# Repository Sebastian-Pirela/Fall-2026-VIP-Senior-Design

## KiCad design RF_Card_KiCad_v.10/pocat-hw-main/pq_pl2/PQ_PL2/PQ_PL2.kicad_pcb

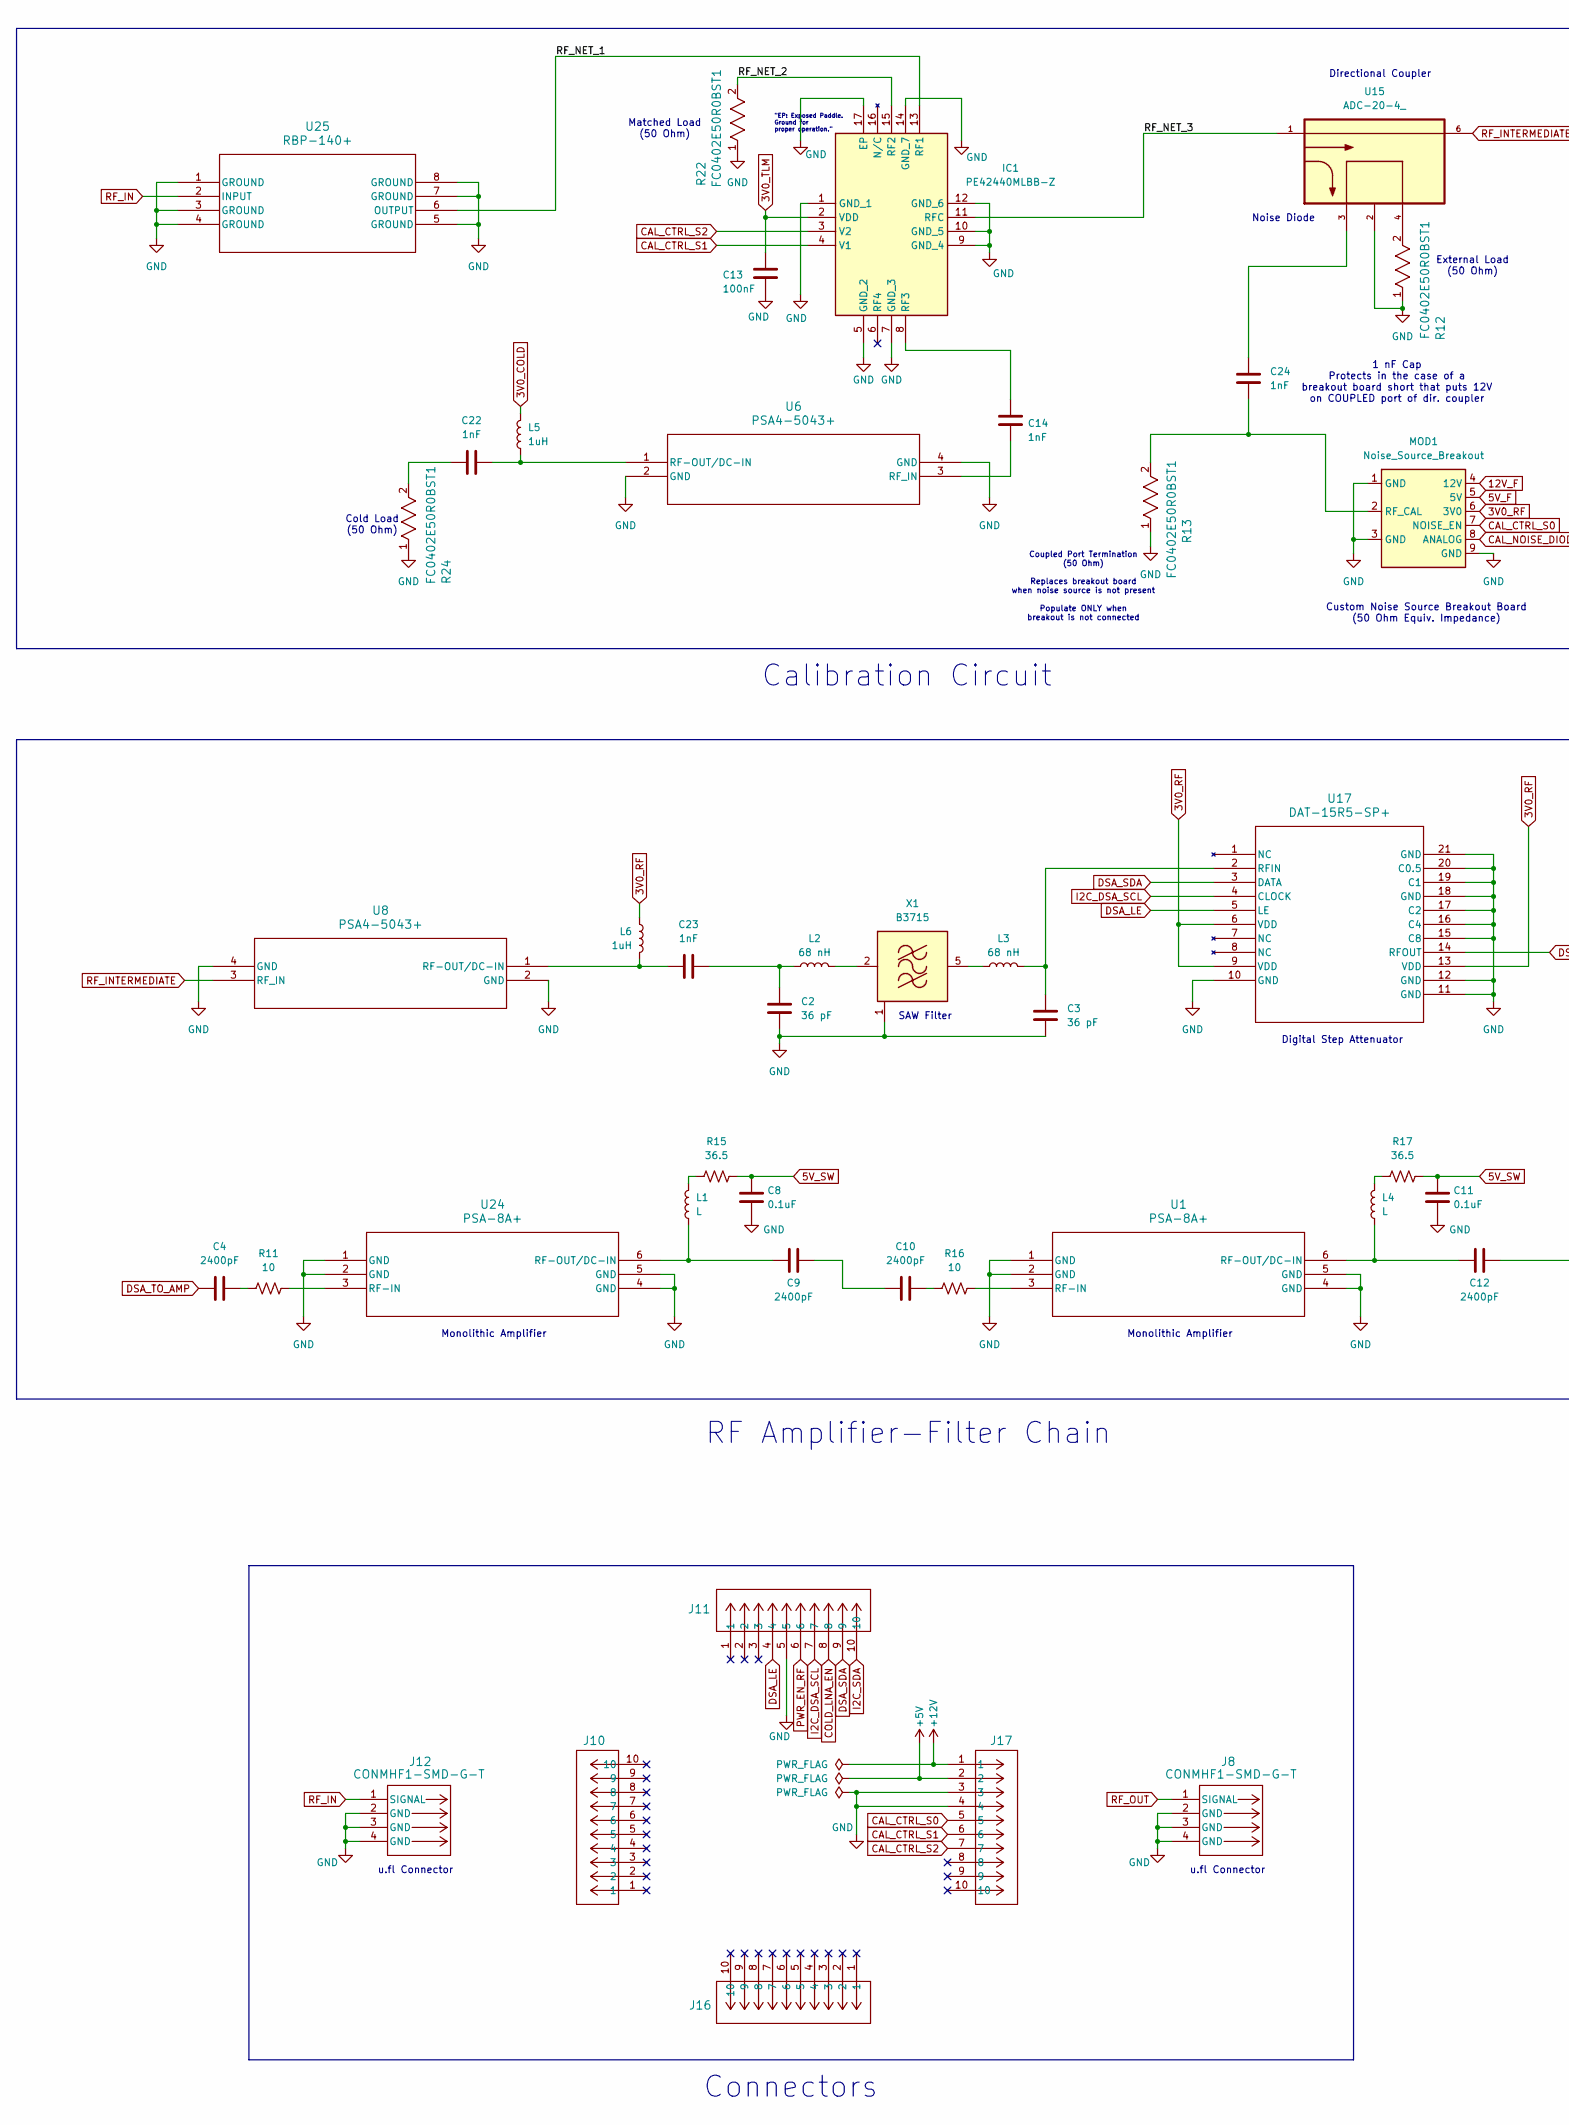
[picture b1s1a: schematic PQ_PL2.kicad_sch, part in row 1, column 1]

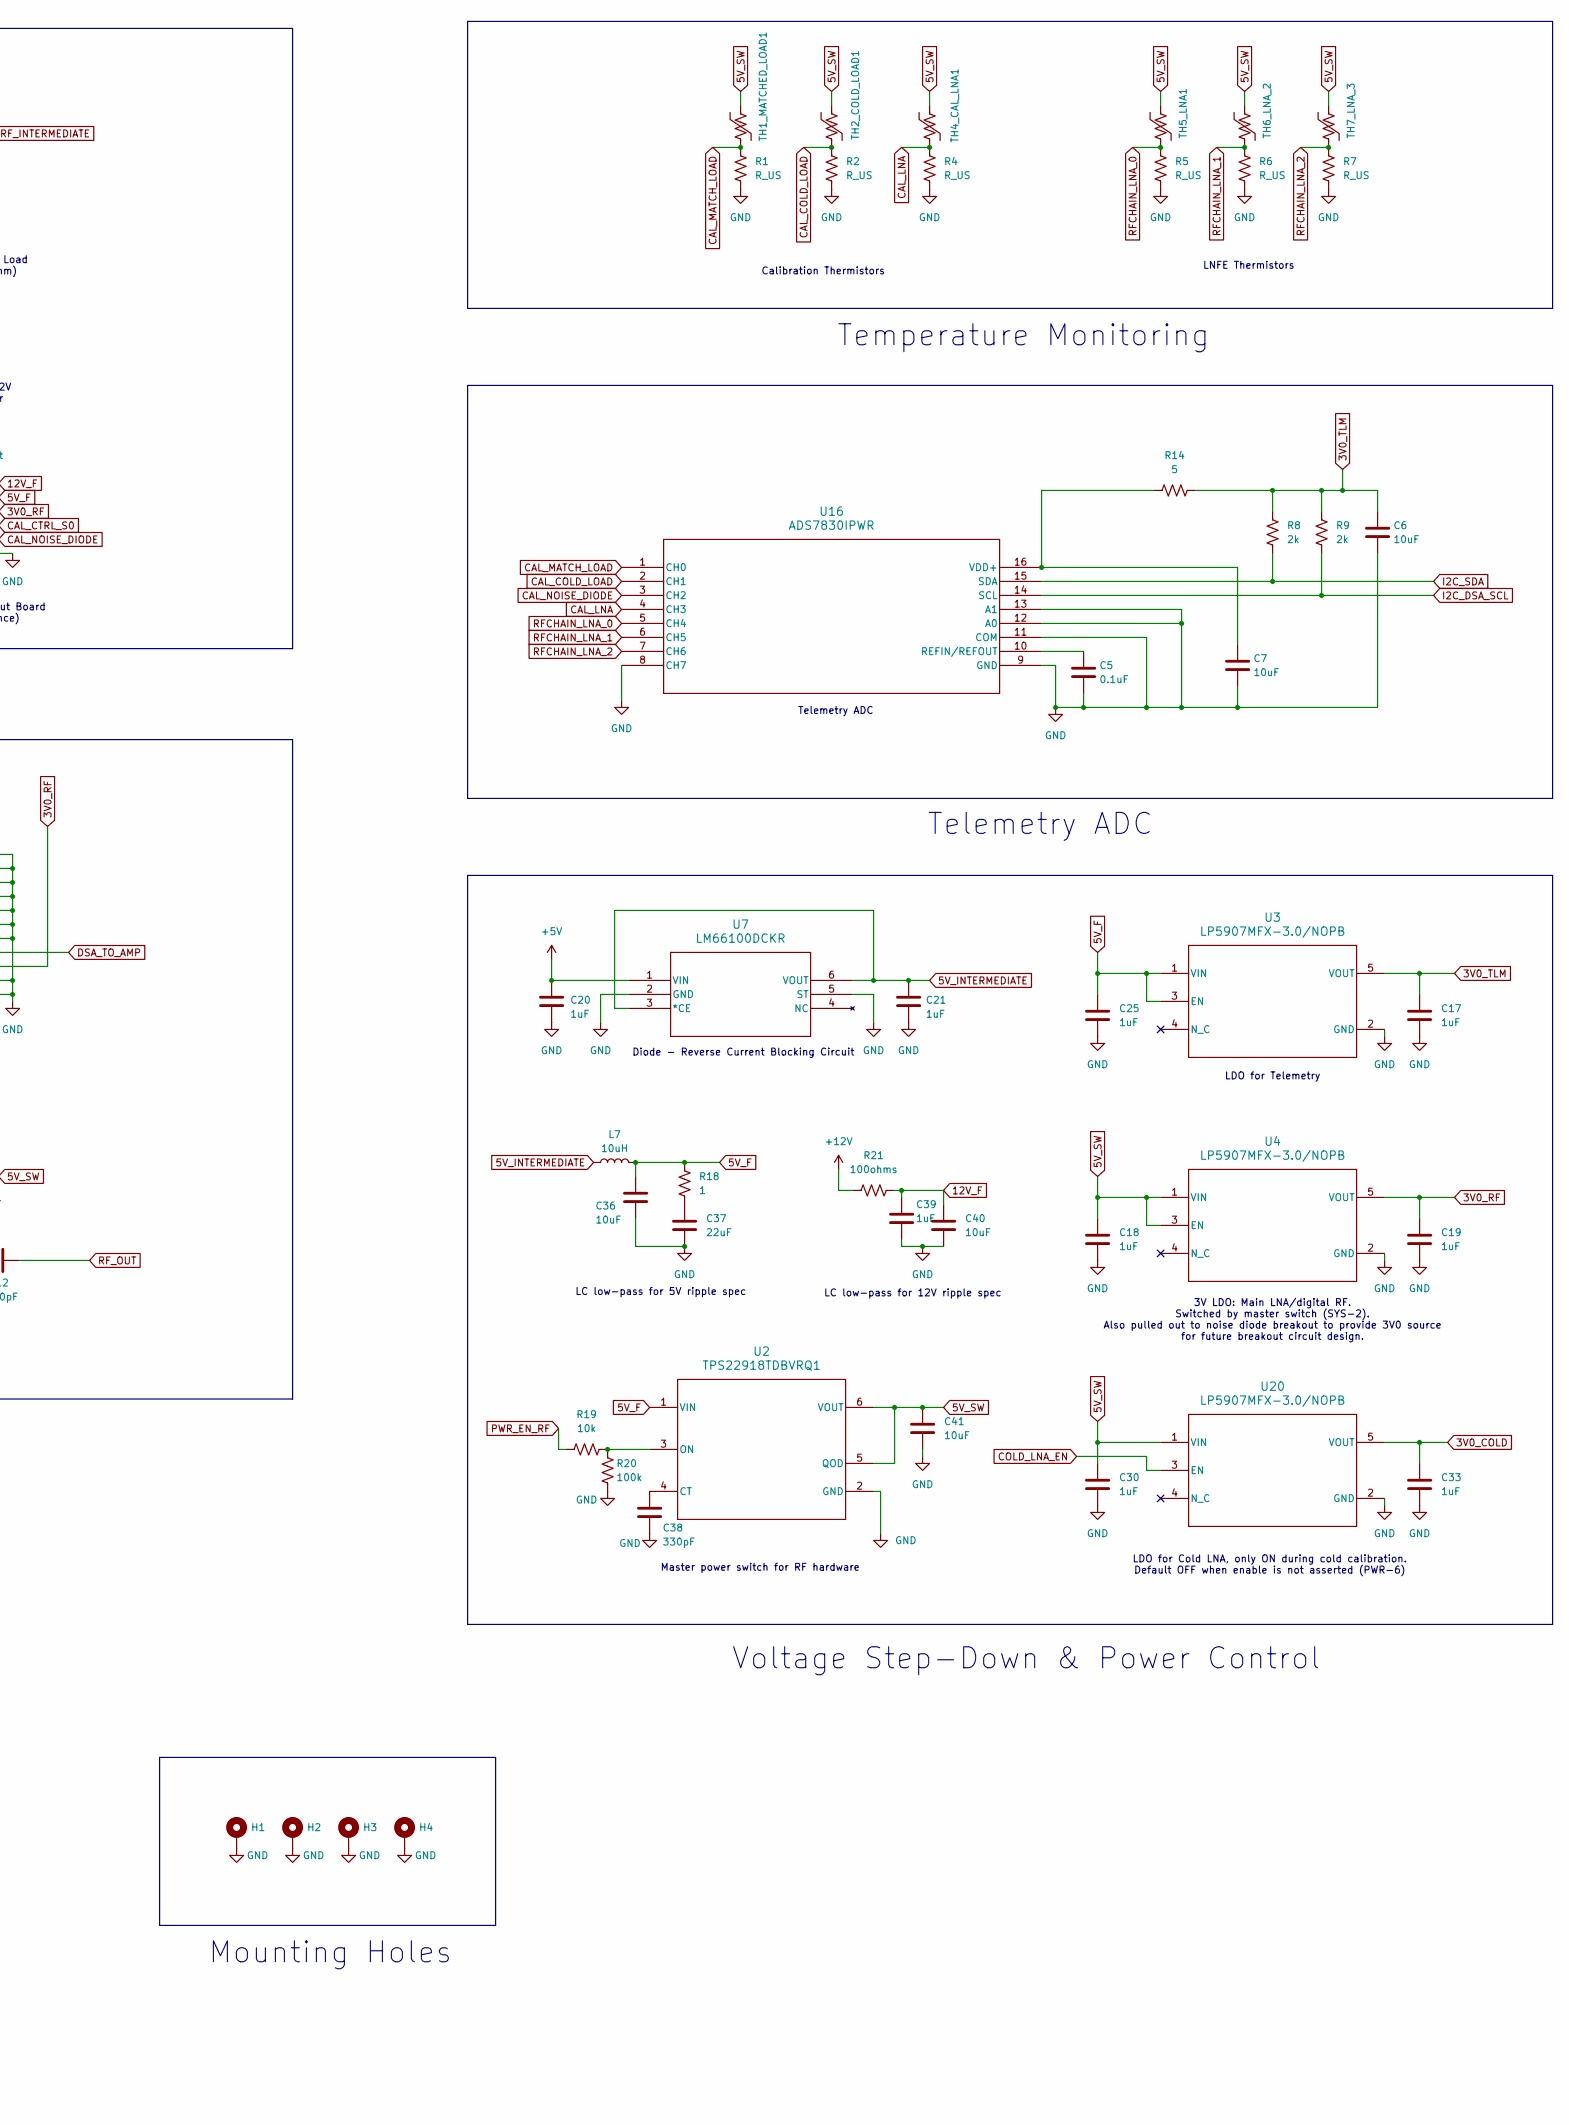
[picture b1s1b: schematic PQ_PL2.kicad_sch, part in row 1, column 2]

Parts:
C2, C3: 36 pF; Resistors_Capacitors_Inductors_0603
C4, C9, C10, C12: 2400pF; Resistors_Capacitors_Inductors_0603
C5, C8, C11: 0.1uF; Resistors_Capacitors_Inductors_0603
C6, C7, C36, C40, C41: 10uF; Resistors_Capacitors_Inductors_0603
C13: 100nF; Resistors_Capacitors_Inductors_0603
C14, C22, C23, C24: 1nF; Resistors_Capacitors_Inductors_0603
C17, C18, C19, C20, C21, C25, C30, C33, C39: 1uF; Resistors_Capacitors_Inductors_0603
C37: 22uF; Resistors_Capacitors_Inductors_0603
C38: 330pF; Resistors_Capacitors_Inductors_0603
H1, H2, H3, H4: MountingHole_Pad; MountingHole_3.2mm_M3_Pad
IC1: PE42440MLBB-Z; ul_PE42440MLBB-Z; Manufacturer_Part_Number PE42440MLBB-Z; Mouser Part Number 81-PE42440MLBB-Z
J8, J12: CONMHF1-SMD-G-T; ul_CONMHF1-SMD-G-T
J10, J11, J16, J17: CES-110-01-T-S; CON10_1X10_TU_SLW_SAI; Manufacturer Part Numbe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 BBL-110-Y-X
L1, L4: L; Resistors_Capacitors_Inductors_0603
L2, L3: 68 nH; Resistors_Capacitors_Inductors_0603
L5, L6: 1uH; Resistors_Capacitors_Inductors_0603
L7: 10uH; Resistors_Capacitors_Inductors_0603
MOD1: Noise_Source_Breakout
R1, R2, R4, R5, R6, R7: R_US; Resistors_Capacitors_Inductors_0603
R8, R9: 2k; Resistors_Capacitors_Inductors_0603
R11, R16: 10; Resistors_Capacitors_Inductors_0603
R12, R13, R22, R24: FC0402E50R0BST1; ul_FC0402E50R0BST1
R14: 5; Resistors_Capacitors_Inductors_0603
R15, R17: 36.5; Resistors_Capacitors_Inductors_0603
R18: 1; Resistors_Capacitors_Inductors_0603
R19: 10k; Resistors_Capacitors_Inductors_0603
R20: 100k; Resistors_Capacitors_Inductors_0603
R21: 100ohms; Resistors_Capacitors_Inductors_0603
TH1_MATCHED_LOAD1, TH2_COLD_LOAD1, TH4_CAL_LNA1, TH5_LNA1, TH6_LNA_2, TH7_LNA_3: Through_Hole_Thermistors
U1, U24: PSA-8A+; ul_PSA-8A-
U2: TPS22918TDBVRQ1; ul_TPS22918TDBVRQ1
U3, U4, U20: LP5907MFX-3.0/NOPB; ul_LP5907MFX-3-0-NOPB
U6, U8: PSA4-5043+; ul_PSA4-5043-
U7: LM66100DCKR; ul_LM66100DCKR
U15: ADC-20-4_; DigiKey_Part_Number 3157-ADC-20-4+CT-ND
U16: ADS7830IPWR; ul_ADS7830IPWR
U17: DAT-15R5-SP+; DG983-2_MNC
U25: RBP-140+; ul_RBP-140- (1)
X1: B3715; ul_TB1103A

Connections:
3V0_COLD: C33.1, L5.2, U20.5 (VOUT)
3V0_RF: C19.1, L6.2, MOD1.6 (3V0), U4.5 (VOUT), U17.6 (VDD), U17.9 (VDD), U17.13 (VDD); also elsewhere on the board
3V0_TLM: C6.1, C13.1, C17.1, IC1.2 (VDD), R8.1, R9.1, R14.2, U3.5 (VOUT); also elsewhere on the board
5V_F: C25.1, C36.2, L7.2, MOD1.5 (5V), R18.1, U2.1 (VIN), U3.1 (VIN), U3.3 (EN); also elsewhere on the board
5V_INTERMEDIATE: C21.1, L7.1, U7.3 (*CE), U7.6 (VOUT)
5V_SW: C8.1, C11.1, C18.1, C30.1, C41.1, R15.2, R17.2, TH1_MATCHED_LOAD1.1, TH2_COLD_LOAD1.1, TH4_CAL_LNA1.1, TH5_LNA1.1, TH6_LNA_2.1, TH7_LNA_3.1, U2.5 (QOD), U2.6 (VOUT), U4.1 (VIN), U4.3 (EN), U20.1 (VIN); also elsewhere on the board
12V_F: C39.1, C40.1, MOD1.4 (12V), R21.2
+5V: C20.1, J17.2, U7.1 (VIN)
+12V: J17.1, R21.1
/RF_NET_1: IC1.13 (RF1), U25.6 (OUTPUT)
/RF_NET_2: IC1.15 (RF2), R22.2
/RF_NET_3: IC1.11 (RFC), U15.1
CAL_COLD_LOAD: R2.1, TH2_COLD_LOAD1.2, U16.2 (CH1)
CAL_CTRL_S0: J17.5, MOD1.7 (NOISE_EN)
CAL_CTRL_S1: IC1.4 (V1), J17.6
CAL_CTRL_S2: IC1.3 (V2), J17.7
CAL_LNA: R4.1, TH4_CAL_LNA1.2, U16.4 (CH3)
CAL_MATCH_LOAD: R1.1, TH1_MATCHED_LOAD1.2, U16.1 (CH0)
CAL_NOISE_DIODE: MOD1.8 (ANALOG), U16.3 (CH2)
COLD_LNA_EN: J11.8, U20.3 (EN)
DSA_LE: J11.4, U17.5 (LE)
DSA_SDA: J11.9, U17.3 (DATA)
DSA_TO_AMP: C4.1, U17.14 (RFOUT)
GND: C2.2, C3.2, C5.2, C6.2, C7.2, C8.2, C11.2, C13.2, C17.2, C18.2, C19.2, C20.2, C21.2, C25.2, C30.2, C33.2, C36.1, C37.2, C38.2, C39.2, C40.2, C41.2, H1.1 (1_1), H2.1 (1_1), H3.1 (1_1), H4.1 (1_1), IC1.1 (GND_1), IC1.5 (GND_2), IC1.7 (GND_3), IC1.9 (GND_4), IC1.10 (GND_5), IC1.12 (GND_6), IC1.14 (GND_7), IC1.17 (EP), J8.2 (GND), J8.3 (GND), J8.4 (GND), J11.5, J12.2 (GND), J12.3 (GND), J12.4 (GND), J17.3, J17.4, MOD1.1 (GND), MOD1.3 (GND), MOD1.9 (GND), R1.2, R2.2, R4.2, R5.2, R6.2, R7.2, R12.1, R13.1, R20.2, R22.1, R24.1, U1.1 (GND), U1.2 (GND), U1.4 (GND), U1.5 (GND), U2.2 (GND), U3.2 (GND), U4.2 (GND), U6.2 (GND), U6.4 (GND), U7.2 (GND), U7.5 (ST), U8.2 (GND), U8.4 (GND), U15.2, U16.8 (CH7), U16.9 (GND), U16.11 (COM), U16.12 (A0), U16.13 (A1), U17.10 (GND), U17.11 (GND), U17.12 (GND), U17.15 (C8), U17.16 (C4), U17.17 (C2), U17.18 (GND), U17.19 (C1), U17.20 (C0.5), U17.21 (GND), U20.2 (GND), U24.1 (GND), U24.2 (GND), U24.4 (GND), U24.5 (GND), U25.1 (GROUND), U25.3 (GROUND), U25.4 (GROUND), U25.5 (GROUND), U25.7 (GROUND), U25.8 (GROUND), X1.1 (GND), X1.3 (GND), X1.4 (GND), X1.6 (GND); also elsewhere on the board
I2C_DSA_SCL: J11.7, R9.2, U16.14 (SCL), U17.4 (CLOCK)
I2C_SDA: J11.10, R8.2, U16.15 (SDA)
unnamed: C2.1, C23.1, L2.1
unnamed: C4.2, R11.1
unnamed: C9.2, C10.1
unnamed: C10.2, R16.1
unnamed: C22.1, R24.2
unnamed: C24.1, U15.3
unnamed: C37.1, R18.2
unnamed: C14.1, IC1.8 (RF3)
unnamed: L1.2, R15.1
unnamed: L4.2, R17.1
unnamed: C24.2, MOD1.2 (RF_CAL), R13.2
unnamed: R12.2, U15.4
unnamed: R16.2, U1.3 (RF-IN)
unnamed: C12.1, L4.1, U1.6 (RF-OUT/DC-IN)
unnamed: C38.1, U2.4 (CT)
unnamed: R19.2, R20.1, U2.3 (ON)
unnamed: C22.2, L5.1, U6.1 (RF-OUT/DC-IN)
unnamed: C14.2, U6.3 (RF_IN)
unnamed: C23.2, L6.1, U8.1 (RF-OUT/DC-IN)
unnamed: C5.1, U16.10 (REFIN/REFOUT)
unnamed: C7.1, R14.1, U16.16 (VDD+)
unnamed: C3.1, L3.2, U17.2 (RFIN)
unnamed: R11.2, U24.3 (RF-IN)
unnamed: C9.1, L1.1, U24.6 (RF-OUT/DC-IN)
unnamed: L2.2, X1.2 (IN)
unnamed: L3.1, X1.5 (OUT)
PWR_EN_RF: J11.6, R19.1
RFCHAIN_LNA_0: R5.1, TH5_LNA1.2, U16.5 (CH4)
RFCHAIN_LNA_1: R6.1, TH6_LNA_2.2, U16.6 (CH5)
RFCHAIN_LNA_2: R7.1, TH7_LNA_3.2, U16.7 (CH6)
RF_IN: J12.1 (SIGNAL), U25.2 (INPUT)
RF_INTERMEDIATE: U8.3 (RF_IN), U15.6
RF_OUT: C12.2, J8.1 (SIGNAL)

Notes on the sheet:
3V LDO: Main LNA/digital RF. Switched by master switch (SYS-2). Also pulled out to noise diode breakout to provide 3V0 source for future breakout circuit design.
Coupled Port Termination (50 Ohm) Replaces breakout board when noise source is not present Populate ONLY when breakout is not connected
Diode - Reverse Current Blocking Circuit
u.fl Connector
Monolithic Amplifier
Directional Coupler
RF Amplifier-Filter Chain
LNFE Thermistors
"EP: Exposed Paddle. Ground for proper operation."
Cold Load (50 Ohm)
1 nF Cap Protects in the case of a breakout board short that puts 12V on COUPLED port of dir. coupler
Digital Step Attenuator
LC low-pass for 12V ripple spec
External Load (50 Ohm)
Master power switch for RF hardware
Temperature Monitoring
Connectors
Noise Diode
LDO for Cold LNA, only ON during cold calibration. Default OFF when enable is not asserted (PWR-6)
LDO for Telemetry
LC low-pass for 5V ripple spec
Mounting Holes
Telemetry ADC
Calibration Circuit
Calibration Thermistors
Custom Noise Source Breakout Board (50 Ohm Equiv. Impedance)
Matched Load (50 Ohm)
Voltage Step-Down & Power Control
SAW Filter

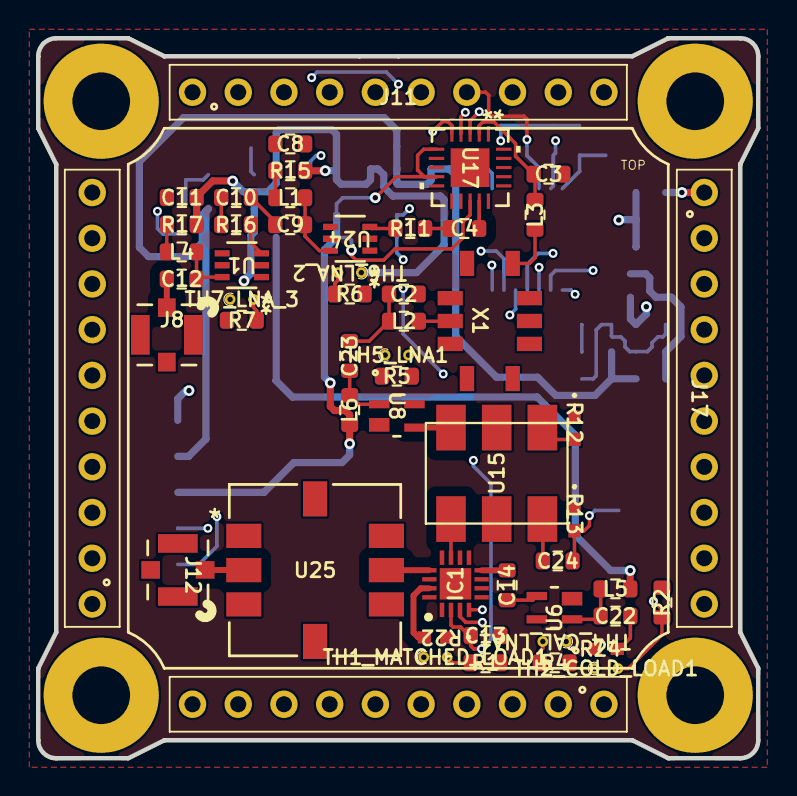
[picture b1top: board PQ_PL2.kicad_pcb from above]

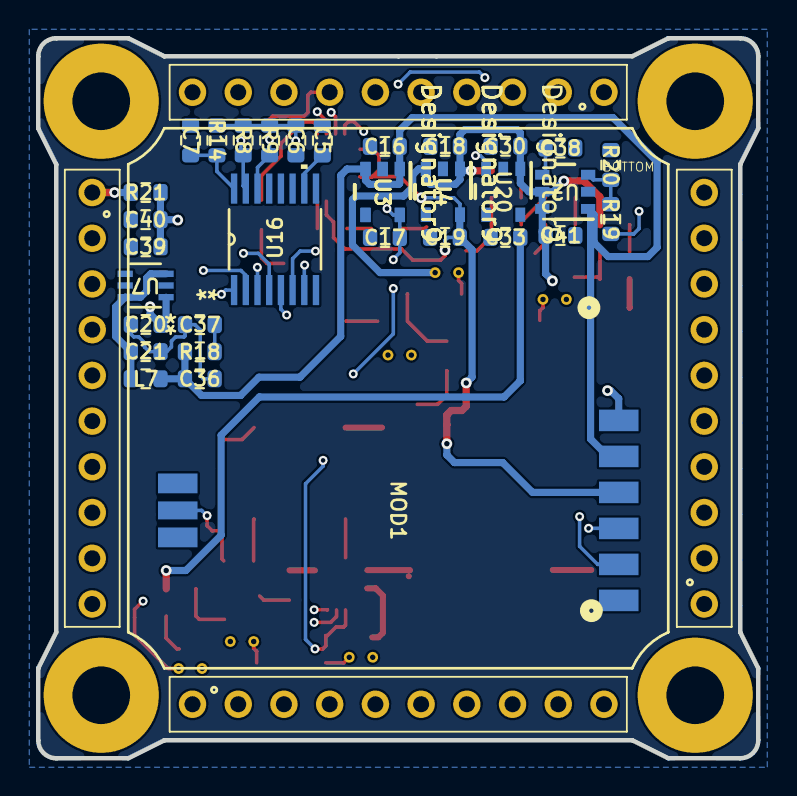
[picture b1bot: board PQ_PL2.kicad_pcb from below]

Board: 4 copper layers, 40.0 x 40.0 mm, 92 parts (34 on the bottom side), 59 nets.

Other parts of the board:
C16: 1uF; Resistors_Capacitors_Inductors_0603
U3#2, U4#2: LP5907MFX-3.0/NOPB; ul_LP5907MFX-3-0-NOPB

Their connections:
3V0_RF: U4#2.5 (VOUT); also elsewhere on the board
3V0_TLM: U3#2.5 (VOUT); also elsewhere on the board
5V_F: C16.1, U3#2.1 (VIN), U3#2.3 (EN); also elsewhere on the board
5V_SW: U4#2.1 (VIN), U4#2.3 (EN); also elsewhere on the board
GND: C16.2, U3#2.2 (GND), U4#2.2 (GND); also elsewhere on the board

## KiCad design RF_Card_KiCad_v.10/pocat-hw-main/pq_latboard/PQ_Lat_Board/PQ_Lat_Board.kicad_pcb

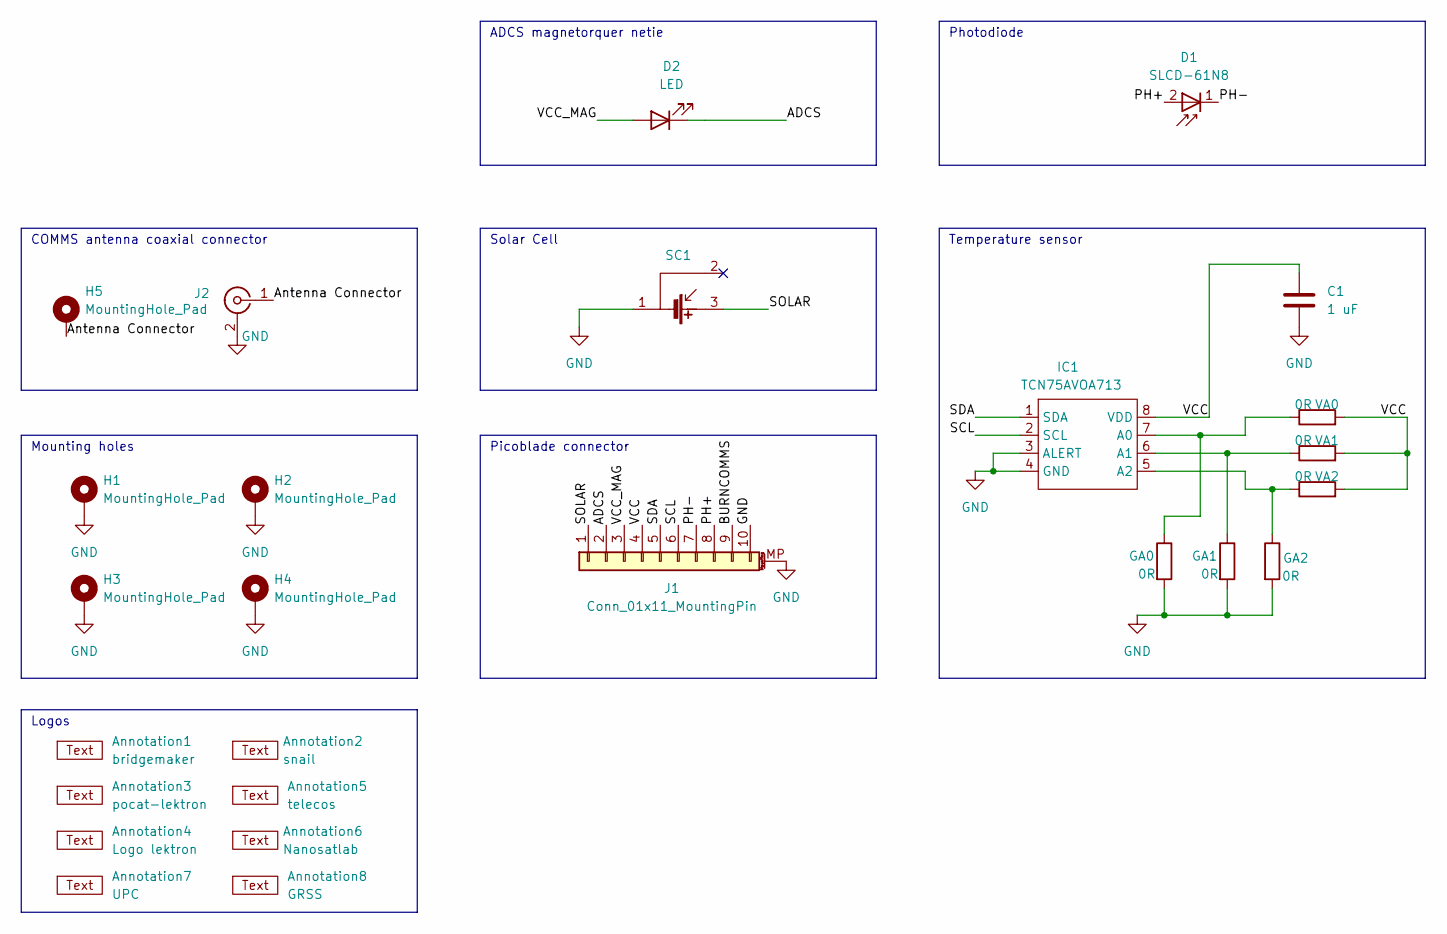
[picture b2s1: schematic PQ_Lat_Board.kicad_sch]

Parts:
Annotation1: bridgemaker; Bridgemaker
Annotation2: snail; Snail
Annotation3: pocat-lektron; pocat_lektron
Annotation4: Logo lektron; NSL_hexagon
Annotation5: telecos; Telecos
Annotation6: Nanosatlab; NSL-small
Annotation7: UPC; UPC_small
Annotation8: GRSS
C1: 1 uF; C_0603_1608Metric; Manufacturer Part Numbe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 GRM188R72A104KA35J
D1: SLCD-61N8; Manufacturer Part Numbe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 SLCD-61N8
D2: LED; LED_0402_1005Metric
GA0, GA1, GA2: 0R; R_0805_2012Metric; Manufacturer Part Numbe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 CRCW08055K00JNTA
H1, H2, H3, H4: MountingHole_Pad; MountingHole_2.2mm_M2_Pad; Manufacturer Part Numbe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 N/A
H5: MountingHole_Pad; MountingHole_2.2mm_M2_DIN965_Pad_TopOnly; Manufacturer Part Numbe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 N/A
IC1: TCN75AVOA713; TCN75AVOA; Manufacturer Part Numbe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 TCN75AVOA
J1: Conn_01x11_MountingPin; Molex_PicoBlade_53261-1071_1x10-1MP_P1.25mm_Horizontal; Manufacturer Part Numbe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 PicoBlade_53261
J2: Conn_Coaxial; U.FL_Hirose_U.FL-R-SMT-1_Vertical
SC1: Lighttricity_S3040_CIC
VA0, VA1, VA2: 0R; R_0805_2012Metric; Manufacturer Part Numbe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 CRCW08055K00JNTA

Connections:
/ADCS: D2.1 (K), J1.2
/Antenna Connector: H5.1 (1_1), J2.1 (In)
/BURNCOMMS: J1.9
/PH+: D1.2, J1.8
/PH-: D1.1, J1.7
/SCL: IC1.2 (SCL), J1.6
/SDA: IC1.1 (SDA), J1.5
/SOLAR: J1.1, SC1.3
/VCC: C1.1, IC1.8 (VDD), J1.4, VA0.2, VA1.2, VA2.2
/VCC_MAG: D2.2 (A), J1.3
GND: C1.2, GA0.2, GA1.2, GA2.2, H1.1 (1_1), H2.1 (1_1), H3.1 (1_1), H4.1 (1_1), IC1.3 (ALERT), IC1.4 (GND), J1.10, J1.MP (MountPin), J2.2 (Ext), SC1.1
unnamed: GA0.1, IC1.7 (A0), VA0.1
unnamed: GA1.1, IC1.6 (A1), VA1.1
unnamed: GA2.1, IC1.5 (A2), VA2.1

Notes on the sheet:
Temperature sensor
Mounting holes
COMMS antenna coaxial connector
Solar Cell
Logos
Photodiode
ADCS magnetorquer netie
Picoblade connector

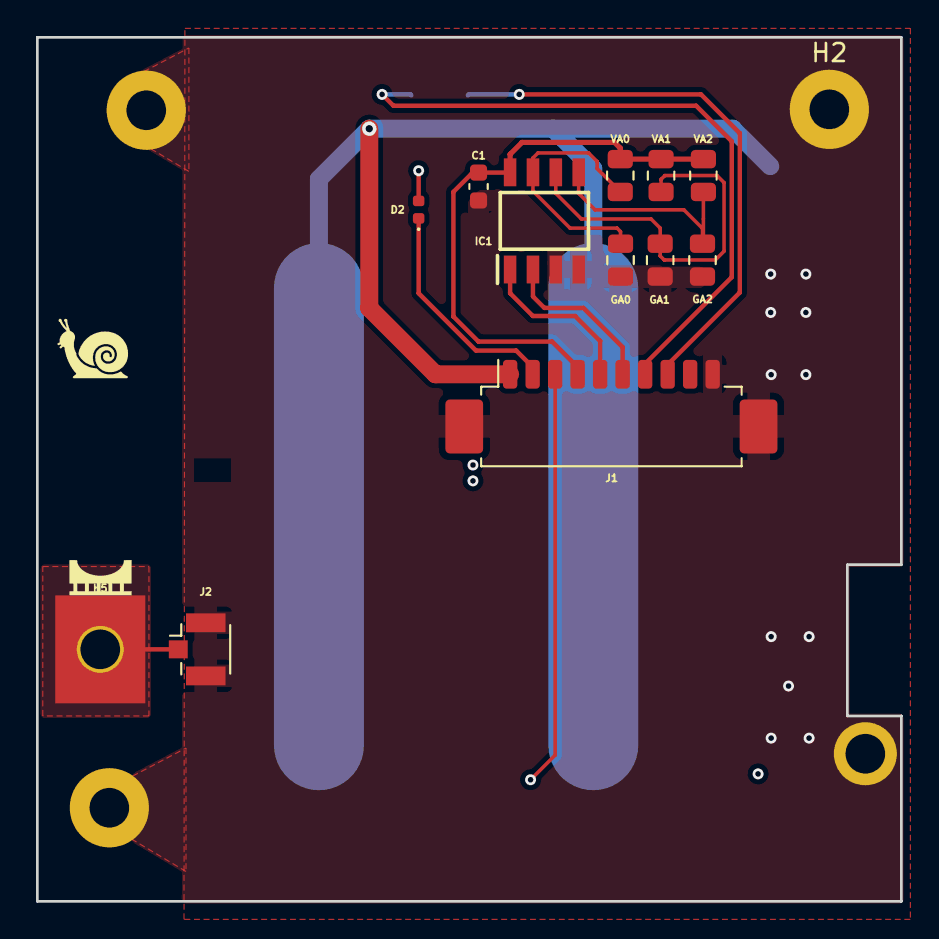
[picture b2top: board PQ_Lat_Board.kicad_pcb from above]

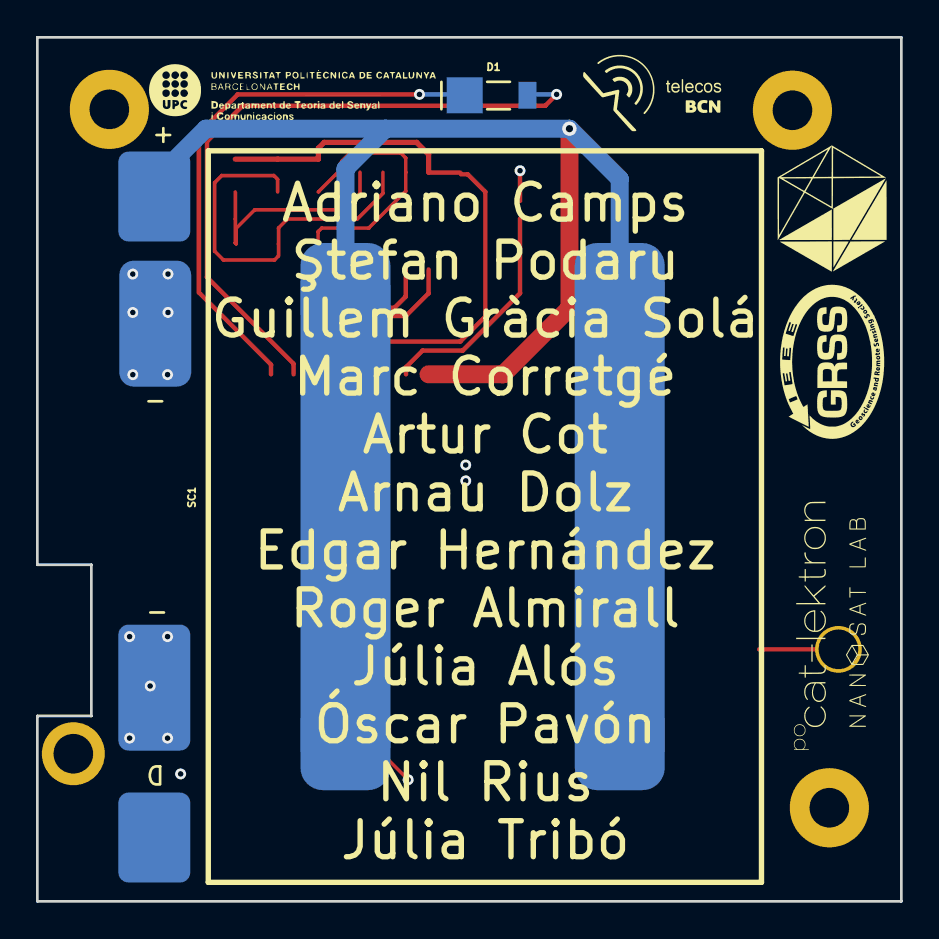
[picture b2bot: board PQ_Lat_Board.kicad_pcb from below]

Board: 6 copper layers, 48.0 x 48.0 mm, 26 parts (8 on the bottom side), 13 nets.

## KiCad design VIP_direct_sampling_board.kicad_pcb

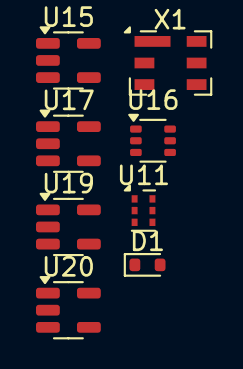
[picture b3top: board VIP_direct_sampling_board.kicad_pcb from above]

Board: 2 copper layers, 8 parts (0 on the bottom side), 4 nets, no tracks yet.

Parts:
D1: GC6002-350A; D_SOD-523
U11: DC4759J5020AHF-1; Anaren_0805_2012Metric-6
U15, U17, U20: LP5907MFX-3.0; SOT-23-5
U16: LM66100DCK; SOT-363_SC-70-6
U19: LP5907MFX-4.5; SOT-23-5
X1: B3715; Filter_SAW_Epcos_DCC6C_3x3mm

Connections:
5V_Diode: U16.3 (~CE), U16.6 (VOUT), U17.1 (IN), U17.3 (EN)
5V_F: U15.1 (IN), U19.1 (IN), U19.3 (EN), U20.1 (IN), U20.3 (EN)
GND: U11.3 (GND), U11.4 (GND), U15.2 (GND), U16.2 (GND), U16.5 (ST), U17.2 (GND), U19.2 (GND), U20.2 (GND), X1.1 (GND), X1.3 (GND), X1.4 (GND), X1.6 (GND)
unnamed: D1.1 (K), U11.2 (Isolated)
